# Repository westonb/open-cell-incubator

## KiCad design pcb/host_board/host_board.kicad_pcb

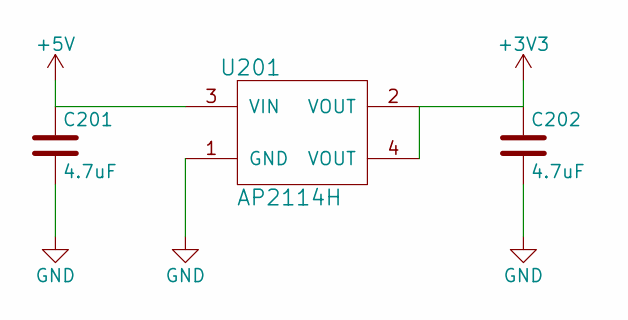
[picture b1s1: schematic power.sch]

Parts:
C201, C202: 4.7uF; C_0603
U201: AP2114H; SOT-223

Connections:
+3V3: C202.1, U201.2 (VOUT), U201.4 (VOUT); also elsewhere on the board
+5V: C201.1, U201.3 (VIN); also elsewhere on the board
GND: C201.2, C202.2, U201.1 (GND); also elsewhere on the board

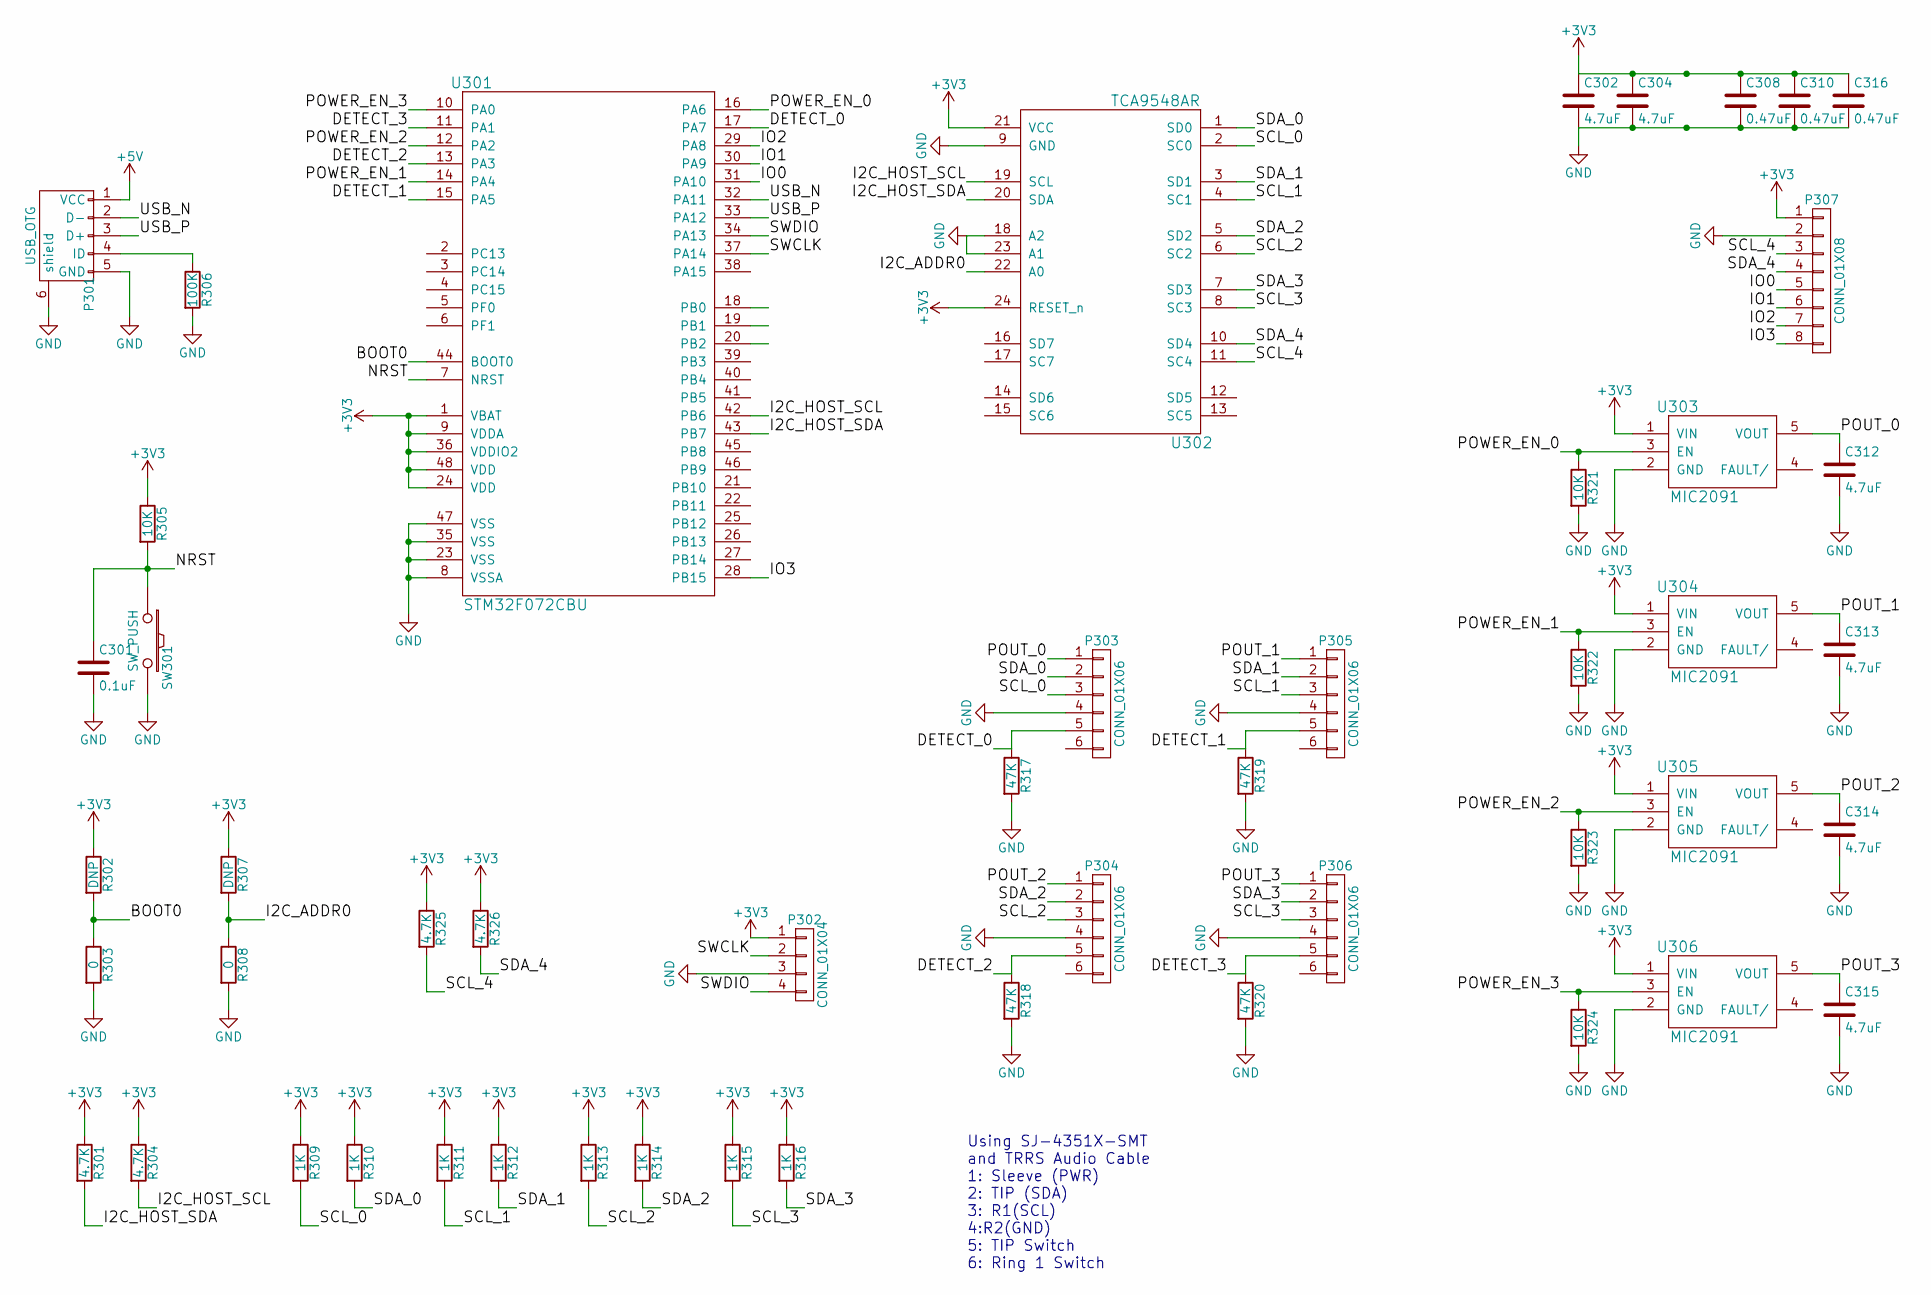
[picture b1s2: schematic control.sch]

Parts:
C301: 0.1uF; C_0603
C302, C304, C312, C313, C314, C315: 4.7uF; C_0603
C308, C310, C316: 0.47uF; C_0603
P301: USB_OTG; USB_Micro-B_10103594-0001LF
P302: CONN_01X04; Pin_Header_Straight_1x04
P303, P304, P305, P306: CONN_01X06; SJ-4351_X-SMT
P307: CONN_01X08; Pin_Header_Straight_1x08
R301, R304, R325, R326: 4.7K; R_0603
R302, R307: DNP; R_0603
R303, R308: 0; R_0603
R305, R321, R322, R323, R324: 10K; R_0603
R306: 100K; R_0603
R309, R310, R311, R312, R313, R314, R315, R316: 1K; R_0603
R317, R318, R319, R320: 47K; R_0603
SW301: SW_PUSH; button-5mm
U301: STM32F072CBU; QFN-48-1EP_7x7mm_Pitch0.5mm
U302: TCA9548AR; QFN-24-1EP_4x4mm_Pitch0.5mm
U303, U304, U305, U306: MIC2091; SOT-23-5

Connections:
+3V3: C302.1, C304.1, C308.1, C310.1, C316.1, P302.1, P307.1, R301.1, R302.1, R304.1, R305.1, R307.1, R309.1, R310.1, R311.1, R312.1, R313.1, R314.1, R315.1, R316.1, R325.1, R326.1, U301.1 (VBAT), U301.9 (VDDA), U301.24 (VDD), U301.36 (VDDIO2), U301.48 (VDD), U302.21 (VCC), U302.24 (RESET_n), U303.1 (VIN), U304.1 (VIN), U305.1 (VIN), U306.1 (VIN); also elsewhere on the board
+5V: P301.1 (VCC); also elsewhere on the board
/Control/BOOT0: R302.2, R303.1, U301.44 (BOOT0)
/Control/DETECT_0: P303.5, R317.1, U301.17 (PA7)
/Control/DETECT_1: P305.5, R319.1, U301.15 (PA5)
/Control/DETECT_2: P304.5, R318.1, U301.13 (PA3)
/Control/DETECT_3: P306.5, R320.1, U301.11 (PA1)
/Control/I2C_ADDR0: R307.2, R308.1, U302.22 (A0)
/Control/I2C_HOST_SCL: R304.2, U301.42 (PB6), U302.19 (SCL)
/Control/I2C_HOST_SDA: R301.2, U301.43 (PB7), U302.20 (SDA)
/Control/IO0: P307.5, U301.31 (PA10)
/Control/IO1: P307.6, U301.30 (PA9)
/Control/IO2: P307.7, U301.29 (PA8)
/Control/IO3: P307.8, U301.28 (PB15)
/Control/NRST: C301.1, R305.2, SW301.1, U301.7 (NRST)
/Control/POUT_0: C312.1, P303.1, U303.5 (VOUT)
/Control/POUT_1: C313.1, P305.1, U304.5 (VOUT)
/Control/POUT_2: C314.1, P304.1, U305.5 (VOUT)
/Control/POUT_3: C315.1, P306.1, U306.5 (VOUT)
/Control/POWER_EN_0: R321.1, U301.16 (PA6), U303.3 (EN)
/Control/POWER_EN_1: R322.1, U301.14 (PA4), U304.3 (EN)
/Control/POWER_EN_2: R323.1, U301.12 (PA2), U305.3 (EN)
/Control/POWER_EN_3: R324.1, U301.10 (PA0), U306.3 (EN)
/Control/SCL_0: P303.3, R309.2, U302.2 (SC0)
/Control/SCL_1: P305.3, R311.2, U302.4 (SC1)
/Control/SCL_2: P304.3, R313.2, U302.6 (SC2)
/Control/SCL_3: P306.3, R315.2, U302.8 (SC3)
/Control/SCL_4: P307.3, R325.2, U302.11 (SC4)
/Control/SDA_0: P303.2, R310.2, U302.1 (SD0)
/Control/SDA_1: P305.2, R312.2, U302.3 (SD1)
/Control/SDA_2: P304.2, R314.2, U302.5 (SD2)
/Control/SDA_3: P306.2, R316.2, U302.7 (SD3)
/Control/SDA_4: P307.4, R326.2, U302.10 (SD4)
/Control/SWCLK: P302.2, U301.37 (PA14)
/Control/SWDIO: P302.4, U301.34 (PA13)
/Control/USB_N: P301.2 (D-), U301.32 (PA11)
/Control/USB_P: P301.3 (D+), U301.33 (PA12)
GND: C301.2, C302.2, C304.2, C308.2, C310.2, C312.2, C313.2, C314.2, C315.2, C316.2, P301.5 (GND), P301.6 (shield), P302.3, P303.4, P304.4, P305.4, P306.4, P307.2, R303.2, R306.2, R308.2, R317.2, R318.2, R319.2, R320.2, R321.2, R322.2, R323.2, R324.2, SW301.2, U301.8 (VSSA), U301.23 (VSS), U301.35 (VSS), U301.47 (VSS), U302.9 (GND), U302.18 (A2), U302.23 (A1), U303.2 (GND), U304.2 (GND), U305.2 (GND), U306.2 (GND); also elsewhere on the board
unnamed: P301.4 (ID), R306.1

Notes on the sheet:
Using SJ-4351X-SMT and TRRS Audio Cable 1: Sleeve (PWR) 2: TIP (SDA) 3: R1(SCL) 4:R2(GND) 5: TIP Switch 6: Ring 1 Switch

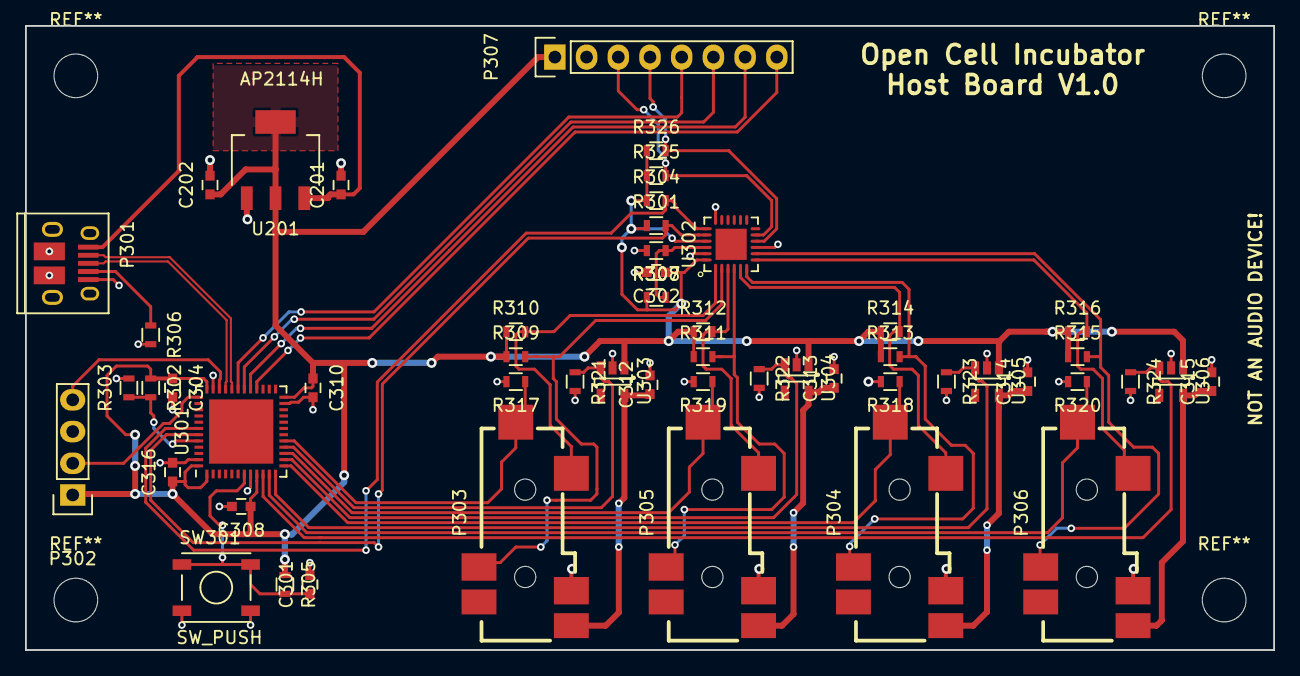
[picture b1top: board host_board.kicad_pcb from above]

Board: 2 copper layers, 100.0 x 50.0 mm, 53 parts (0 on the bottom side), 39 nets.

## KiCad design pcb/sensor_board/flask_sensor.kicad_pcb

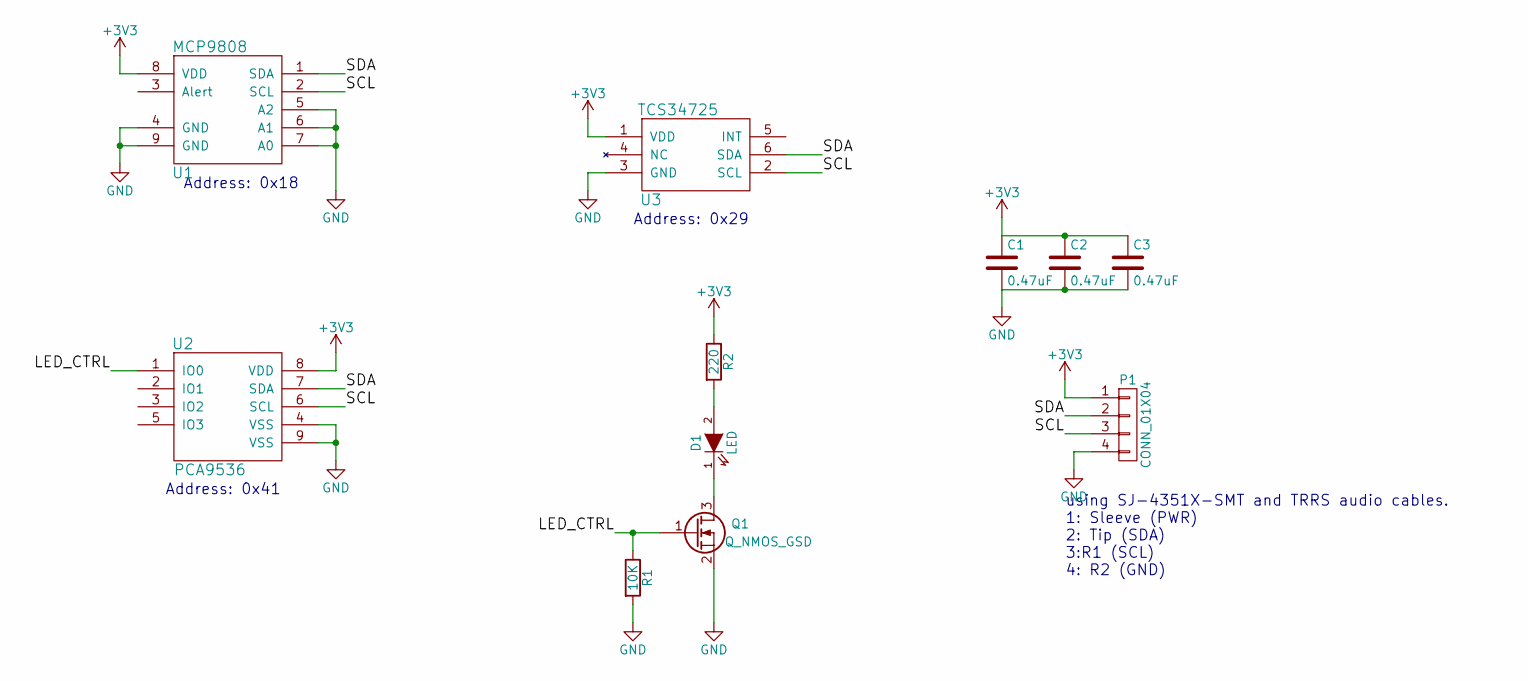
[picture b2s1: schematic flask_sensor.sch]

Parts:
C1, C2, C3: 0.47uF; C_0603
D1: LED; LM561B-LED
P1: CONN_01X04; SJ-4351_X-SMT
Q1: Q_NMOS_GSD; SOT-23
R1: 10K; R_0603
R2: 220; R_0805
U1: MCP9808; DFN-8-1EP_3x2mm_Pitch0.5mm
U2: PCA9536; DFN-8-1EP_3x3mm_Pitch0.5mm
U3: TCS34725; FN-6(TCS3472x)

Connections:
+3V3: C1.1, C2.1, C3.1, P1.1, R2.1, U1.8 (VDD), U2.8 (VDD), U3.1 (VDD)
/LED_CTRL: Q1.1 (G), R1.1, U2.1 (IO0)
/SCL: P1.3, U1.2 (SCL), U2.6 (SCL), U3.2 (SCL)
/SDA: P1.2, U1.1 (SDA), U2.7 (SDA), U3.6 (SDA)
GND: C1.2, C2.2, C3.2, P1.4, Q1.2 (S), R1.2, U1.4 (GND), U1.5 (A2), U1.6 (A1), U1.7 (A0), U1.9 (GND), U2.4 (VSS), U2.9 (VSS), U3.3 (GND)
unnamed: D1.1 (K), Q1.3 (D)
unnamed: D1.2 (A), R2.2

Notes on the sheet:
Address: 0x41
Address: 0x29
Address: 0x18
using SJ-4351X-SMT and TRRS audio cables. 1: Sleeve (PWR) 2: Tip (SDA) 3:R1 (SCL) 4: R2 (GND)

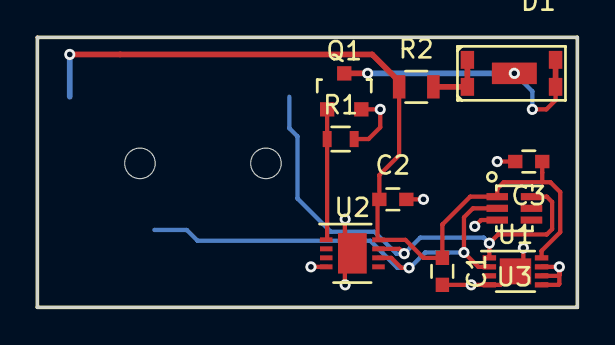
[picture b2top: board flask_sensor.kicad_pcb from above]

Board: 2 copper layers, 30.0 x 15.0 mm, 11 parts (1 on the bottom side), 7 nets.

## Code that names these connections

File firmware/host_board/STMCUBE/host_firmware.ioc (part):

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Mcu.Name=STM32F072C(8-B)Ux
Mcu.Package=UFQFPN48
Mcu.UserName=STM32F072CBUx
PA0.Signal=GPIO_Output
PA1.Signal=GPIO_Input
PA11.Mode=Device
PA11.Signal=USB_DM
PA12.Mode=Device
PA12.Signal=USB_DP
PA2.Signal=GPIO_Output
PA3.Signal=GPIO_Input
PA4.Signal=GPIO_Output
PA5.Signal=GPIO_Input
PA6.Signal=GPIO_Output
PA7.Signal=GPIO_Input
PB6.Mode=I2C
PB6.Signal=I2C1_SCL
PB7.Mode=I2C
PB7.Signal=I2C1_SDA
RCC.SYSCLKFreq_VALUE=48000000
RCC.SYSCLKSource=RCC_SYSCLKSOURCE_HSI48

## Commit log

2016-02-26 designed host board
2016-04-03 setup toolchain
2016-04-11 got usb working
2016-04-25 fixed linker file, got basic data logging over USB working
2017-02-19 added pdb schematic
